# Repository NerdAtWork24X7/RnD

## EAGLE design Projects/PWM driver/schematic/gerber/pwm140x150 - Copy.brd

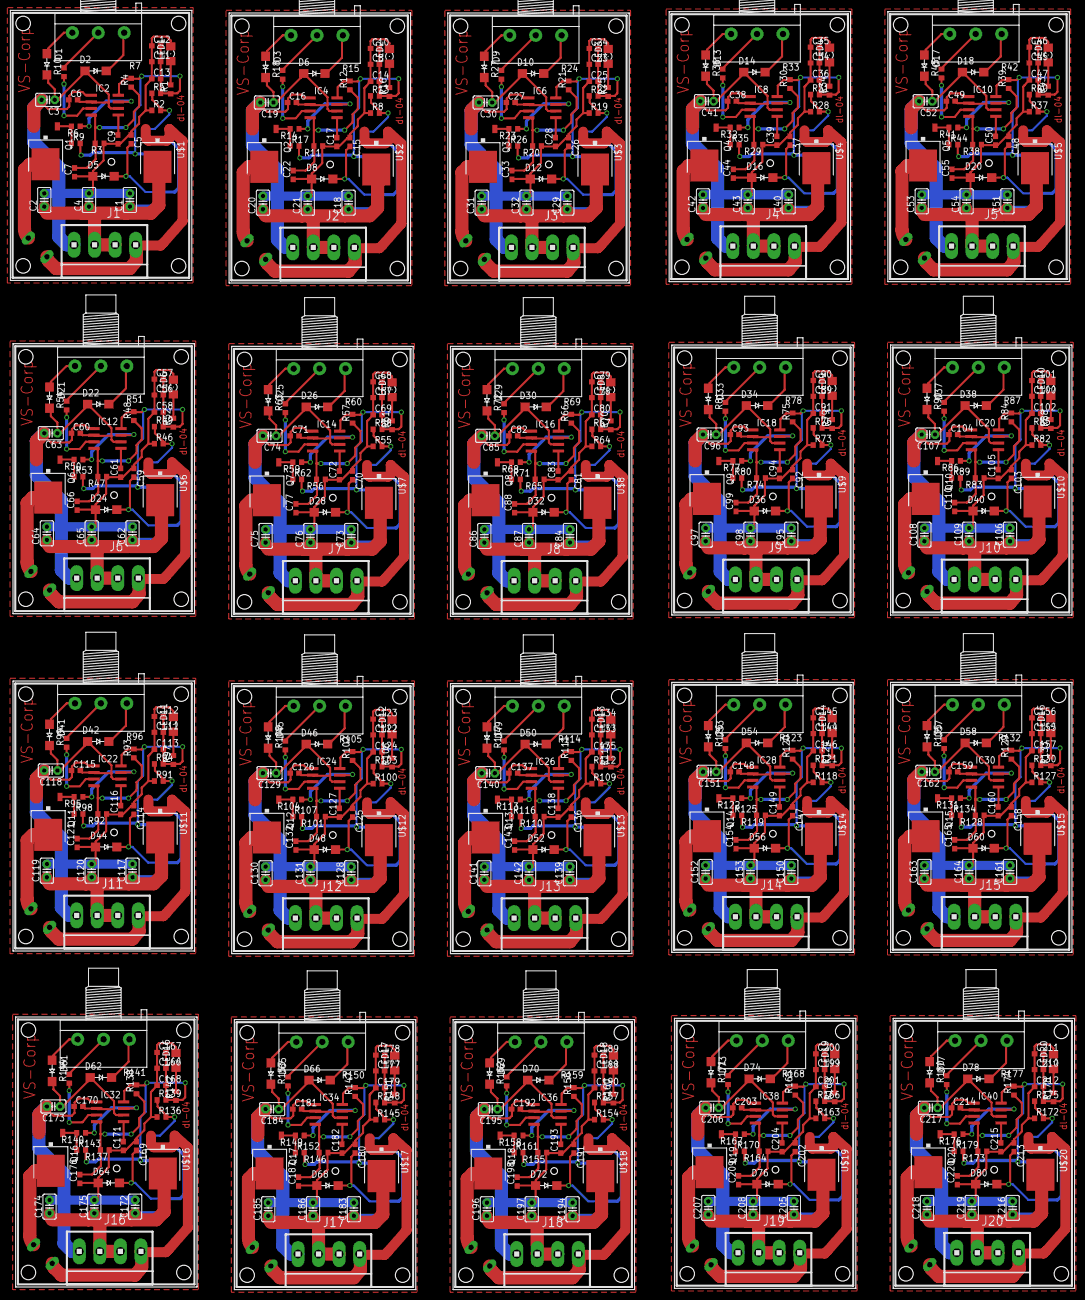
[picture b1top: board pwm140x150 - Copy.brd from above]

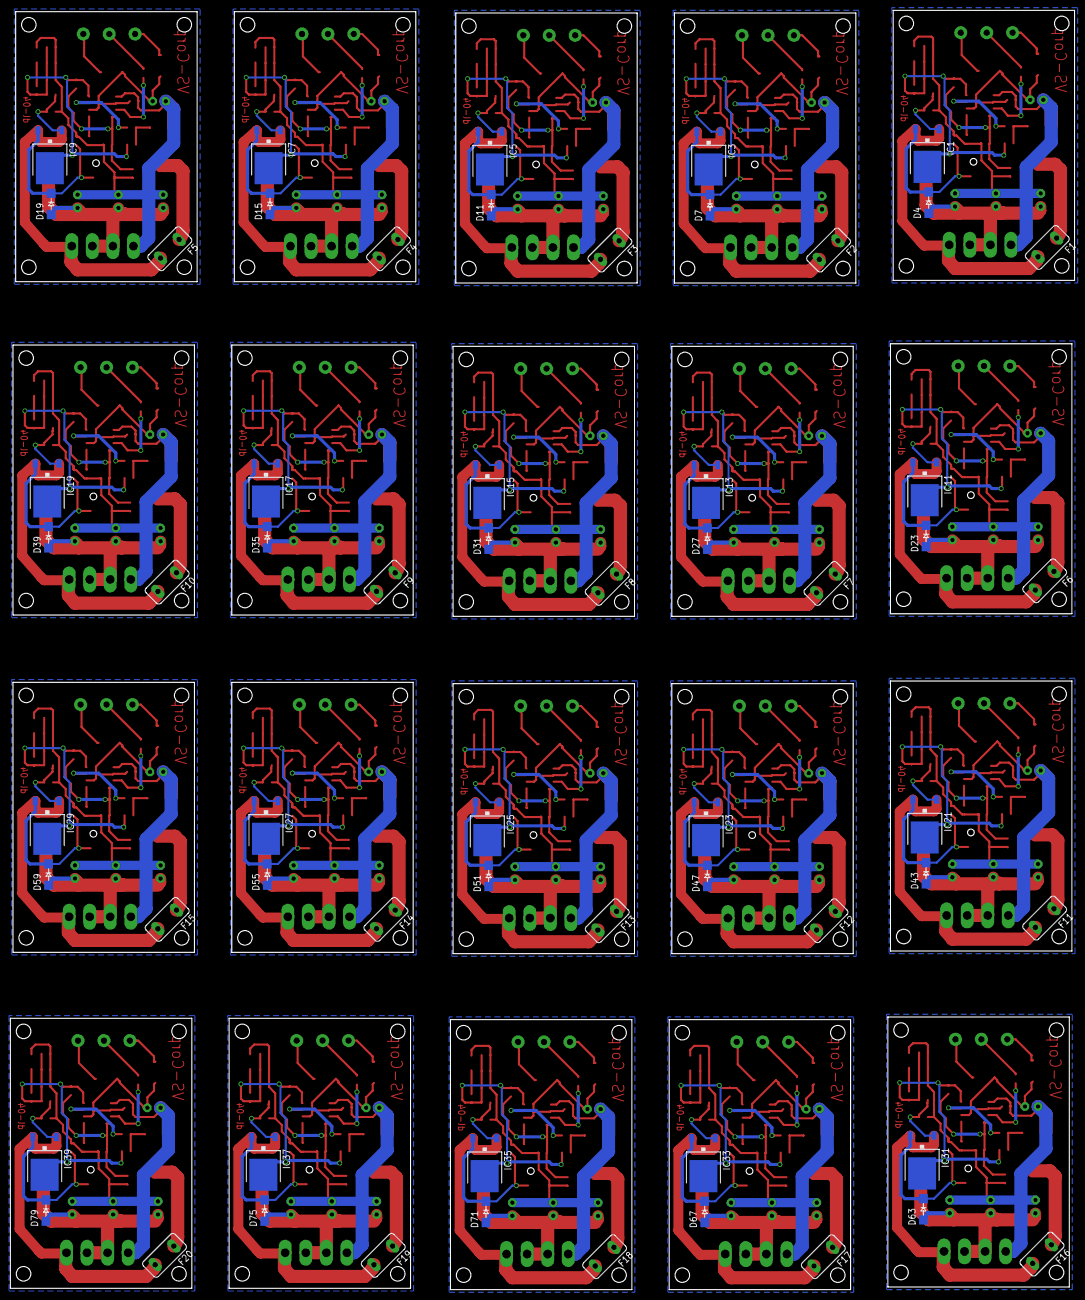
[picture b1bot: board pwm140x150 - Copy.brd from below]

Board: 2 copper layers, 205.2 x 246.6 mm, 620 parts (60 on the bottom side), 340 nets.

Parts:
C1, C18, C29, C40, C51, C62, C73, C84, C95, C106, C117, C128, C139, C150, C161, C172, C183, C194, C205, C216: C025-025X050
C2, C4, C20, C21, C31, C32, C42, C43, C53, C54, C64, C65, C75, C76, C86, C87, C97, C98, C108, C109, C119, C120, C130, C131, C141, C142, C152, C153, C163, C164, C174, C175, C185, C186, C196, C197, C207, C208, C218, C219: 220uf; C025-025X050
C3, C19, C30, C41, C52, C63, C74, C85, C96, C107, C118, C129, C140, C151, C162, C173, C184, C195, C206, C217: 0.1uf; C025-025X050
C5, C15, C26, C37, C48, C59, C70, C81, C92, C103, C114, C125, C136, C147, C158, C169, C180, C191, C202, C213: 100nf; C0603
C6, C16, C27, C38, C49, C60, C71, C82, C93, C104, C115, C126, C137, C148, C159, C170, C181, C192, C203, C214: 0.1uF; C0603
C7, C22, C33, C44, C55, C66, C77, C88, C99, C110, C121, C132, C143, C154, C165, C176, C187, C198, C209, C220: 220uf; C0603
C8, C11, C23, C34, C45, C56, C67, C78, C89, C100, C111, C122, C133, C144, C155, C166, C177, C188, C199, C210: 100nF; C0603
C9, C10, C12, C17, C24, C28, C35, C39, C46, C50, C57, C61, C68, C72, C79, C83, C90, C94, C101, C105, C112, C116, C123, C127, C134, C138, C145, C149, C156, C160, C167, C171, C178, C182, C189, C193, C200, C204, C211, C215: 10nF; C0603
C13, C14, C25, C36, C47, C58, C69, C80, C91, C102, C113, C124, C135, C146, C157, C168, C179, C190, C201, C212: 1uF; C0603
D1, D2, D3, D6, D9, D10, D13, D14, D17, D18, D21, D22, D25, D26, D29, D30, D33, D34, D37, D38, D41, D42, D45, D46, D49, D50, D53, D54, D57, D58, D61, D62, D65, D66, D69, D70, D73, D74, D77, D78: FM4007; SMA-DO214AC
D4, D7, D11, D15, D19, D23, D27, D31, D35, D39, D43, D47, D51, D55, D59, D63, D67, D71, D75, D79: Fm4007; SMA-DO214AC
D5, D8, D12, D16, D20, D24, D28, D32, D36, D40, D44, D48, D52, D56, D60, D64, D68, D72, D76, D80: 1N34; SMA-DO214AC
F1, F2, F3, F4, F5, F6, F7, F8, F9, F10, F11, F12, F13, F14, F15, F16, F17, F18, F19, F20: FUSETE5; TE5
IC1, IC3, IC5, IC7, IC9, IC11, IC13, IC15, IC17, IC19, IC21, IC23, IC25, IC27, IC29, IC31, IC33, IC35, IC37, IC39: 317; DPACK
IC2, IC4, IC6, IC8, IC10, IC12, IC14, IC16, IC18, IC20, IC22, IC24, IC26, IC28, IC30, IC32, IC34, IC36, IC38, IC40: LM555D; SO08
J1, J2, J3, J4, J5, J6, J7, J8, J9, J10, J11, J12, J13, J14, J15, J16, J17, J18, J19, J20: 1X4MTA
LED1, LED2, LED3, LED4, LED5, LED6, LED7, LED8, LED9, LED10, LED11, LED12, LED13, LED14, LED15, LED16, LED17, LED18, LED19, LED20: LED_1206
Q1, Q2, Q3, Q4, Q5, Q6, Q7, Q8, Q9, Q10, Q11, Q12, Q13, Q14, Q15, Q16, Q17, Q18, Q19, Q20: FDD4141TO252; TO252
R1, R5, R13, R16, R22, R25, R31, R34, R40, R43, R49, R52, R58, R61, R67, R70, R76, R79, R85, R88, R94, R97, R103, R106, R112, R115, R121, R124, R130, R133, R139, R142, R148, R151, R157, R160, R166, R169, R175, R178: 470; R0603
R2, R8, R19, R28, R37, R46, R55, R64, R73, R82, R91, R100, R109, R118, R127, R136, R145, R154, R163, R172: 1.5k; R0603
R3, R11, R20, R29, R38, R47, R56, R65, R74, R83, R92, R101, R110, R119, R128, R137, R146, R155, R164, R173: 330k; R0603
R4, R12, R21, R30, R39, R48, R57, R66, R75, R84, R93, R102, R111, R120, R129, R138, R147, R156, R165, R174: 150k; R0603
R6, R14, R23, R32, R41, R50, R59, R68, R77, R86, R95, R104, R113, R122, R131, R140, R149, R158, R167, R176: 1k; R0603
R7, R15, R24, R33, R42, R51, R60, R69, R78, R87, R96, R105, R114, R123, R132, R141, R150, R159, R168, R177: 3RP/1610N
R9, R17, R26, R35, R44, R53, R62, R71, R80, R89, R98, R107, R116, R125, R134, R143, R152, R161, R170, R179: 47k; R0603
R10, R18, R27, R36, R45, R54, R63, R72, R81, R90, R99, R108, R117, R126, R135, R144, R153, R162, R171, R180: 0r0; R0603
U$1, U$2, U$3, U$4, U$5, U$6, U$7, U$8, U$9, U$10, U$11, U$12, U$13, U$14, U$15, U$16, U$17, U$18, U$19, U$20: DIODE; DPACK

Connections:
GND: C1.2, C2.2, C3.2, C4.2, C5.1, C6.1, C7.1, C9.1, C11.1, C12.1, C13.1, D5.A, IC2.1, J1.1, LED1.C, Q1.2, R2.1, R3.1
GND1: C8.1, C10.1, C14.1, C15.1, C16.1, C17.1, C18.2, C19.2, C20.2, C21.2, C22.1, D8.A, IC4.1, J2.1, LED2.C, Q2.2, R8.1, R11.1
GND2: C23.1, C24.1, C25.1, C26.1, C27.1, C28.1, C29.2, C30.2, C31.2, C32.2, C33.1, D12.A, IC6.1, J3.1, LED3.C, Q3.2, R19.1, R20.1
GND3: C34.1, C35.1, C36.1, C37.1, C38.1, C39.1, C40.2, C41.2, C42.2, C43.2, C44.1, D16.A, IC8.1, J4.1, LED4.C, Q4.2, R28.1, R29.1
GND4: C45.1, C46.1, C47.1, C48.1, C49.1, C50.1, C51.2, C52.2, C53.2, C54.2, C55.1, D20.A, IC10.1, J5.1, LED5.C, Q5.2, R37.1, R38.1
GND5: C56.1, C57.1, C58.1, C59.1, C60.1, C61.1, C62.2, C63.2, C64.2, C65.2, C66.1, D24.A, IC12.1, J6.1, LED6.C, Q6.2, R46.1, R47.1
GND6: C67.1, C68.1, C69.1, C70.1, C71.1, C72.1, C73.2, C74.2, C75.2, C76.2, C77.1, D28.A, IC14.1, J7.1, LED7.C, Q7.2, R55.1, R56.1
GND7: C78.1, C79.1, C80.1, C81.1, C82.1, C83.1, C84.2, C85.2, C86.2, C87.2, C88.1, D32.A, IC16.1, J8.1, LED8.C, Q8.2, R64.1, R65.1
GND8: C89.1, C90.1, C91.1, C92.1, C93.1, C94.1, C95.2, C96.2, C97.2, C98.2, C99.1, D36.A, IC18.1, J9.1, LED9.C, Q9.2, R73.1, R74.1
GND9: C100.1, C101.1, C102.1, C103.1, C104.1, C105.1, C106.2, C107.2, C108.2, C109.2, C110.1, D40.A, IC20.1, J10.1, LED10.C, Q10.2, R82.1, R83.1
GND10: C111.1, C112.1, C113.1, C114.1, C115.1, C116.1, C117.2, C118.2, C119.2, C120.2, C121.1, D44.A, IC22.1, J11.1, LED11.C, Q11.2, R91.1, R92.1
GND11: C122.1, C123.1, C124.1, C125.1, C126.1, C127.1, C128.2, C129.2, C130.2, C131.2, C132.1, D48.A, IC24.1, J12.1, LED12.C, Q12.2, R100.1, R101.1
GND12: C133.1, C134.1, C135.1, C136.1, C137.1, C138.1, C139.2, C140.2, C141.2, C142.2, C143.1, D52.A, IC26.1, J13.1, LED13.C, Q13.2, R109.1, R110.1
GND13: C144.1, C145.1, C146.1, C147.1, C148.1, C149.1, C150.2, C151.2, C152.2, C153.2, C154.1, D56.A, IC28.1, J14.1, LED14.C, Q14.2, R118.1, R119.1
GND14: C155.1, C156.1, C157.1, C158.1, C159.1, C160.1, C161.2, C162.2, C163.2, C164.2, C165.1, D60.A, IC30.1, J15.1, LED15.C, Q15.2, R127.1, R128.1
GND15: C166.1, C167.1, C168.1, C169.1, C170.1, C171.1, C172.2, C173.2, C174.2, C175.2, C176.1, D64.A, IC32.1, J16.1, LED16.C, Q16.2, R136.1, R137.1
GND16: C177.1, C178.1, C179.1, C180.1, C181.1, C182.1, C183.2, C184.2, C185.2, C186.2, C187.1, D68.A, IC34.1, J17.1, LED17.C, Q17.2, R145.1, R146.1
GND17: C188.1, C189.1, C190.1, C191.1, C192.1, C193.1, C194.2, C195.2, C196.2, C197.2, C198.1, D72.A, IC36.1, J18.1, LED18.C, Q18.2, R154.1, R155.1
GND18: C199.1, C200.1, C201.1, C202.1, C203.1, C204.1, C205.2, C206.2, C207.2, C208.2, C209.1, D76.A, IC38.1, J19.1, LED19.C, Q19.2, R163.1, R164.1
GND19: C210.1, C211.1, C212.1, C213.1, C214.1, C215.1, C216.2, C217.2, C218.2, C219.2, C220.1, D80.A, IC40.1, J20.1, LED20.C, Q20.2, R172.1, R173.1
unnamed: C7.2, IC2.4, R3.2, R4.1
unnamed: C3.1, C6.2, D1.K, D2.A, IC2.2, IC2.6
unnamed: D1.A, R7.3
unnamed: D2.K, R7.1
unnamed: R7.2, R10.2
unnamed: IC2.3, R10.1
unnamed: C9.2, IC2.5
unnamed: C5.2, D4.K, D5.K, IC1.VIN
unnamed: Q1.1, R6.2, R9.1
unnamed: IC2.7, R6.1
unnamed: LED1.A, R1.2
unnamed: D3.A, R15.3
unnamed: IC1.ADJ, R2.2, R5.1
unnamed: F1.1, Q1.3
unnamed: F1.2, J1.4, U$1.ADJ, U$1.VIN
unnamed: D6.K, R15.1
unnamed: C17.2, IC4.5
unnamed: C16.2, C19.1, D3.K, D6.A, IC4.2, IC4.6
unnamed: Q2.1, R14.2, R17.1
unnamed: C22.2, IC4.4, R11.2, R12.1
unnamed: IC4.3, R18.1
unnamed: IC4.7, R14.1
unnamed: C15.2, D7.K, D8.K, IC3.VIN
unnamed: LED2.A, R16.2
unnamed: IC3.ADJ, R8.2, R13.1
unnamed: F2.1, Q2.3
unnamed: F2.2, J2.4, U$2.ADJ, U$2.VIN
unnamed: R15.2, R18.2
unnamed: D9.A, R24.3
unnamed: D10.K, R24.1
unnamed: C28.2, IC6.5
unnamed: C27.2, C30.1, D9.K, D10.A, IC6.2, IC6.6
unnamed: Q3.1, R23.2, R26.1
unnamed: C33.2, IC6.4, R20.2, R21.1
unnamed: IC6.3, R27.1
unnamed: IC6.7, R23.1
unnamed: C26.2, D11.K, D12.K, IC5.VIN
unnamed: LED3.A, R25.2
unnamed: IC5.ADJ, R19.2, R22.1
unnamed: F3.1, Q3.3
unnamed: F3.2, J3.4, U$3.ADJ, U$3.VIN
unnamed: R24.2, R27.2
unnamed: D13.A, R33.3
unnamed: D14.K, R33.1
unnamed: C39.2, IC8.5
unnamed: C38.2, C41.1, D13.K, D14.A, IC8.2, IC8.6
unnamed: Q4.1, R32.2, R35.1
unnamed: C44.2, IC8.4, R29.2, R30.1
unnamed: IC8.3, R36.1
unnamed: IC8.7, R32.1
unnamed: C37.2, D15.K, D16.K, IC7.VIN
unnamed: LED4.A, R34.2
unnamed: IC7.ADJ, R28.2, R31.1
unnamed: F4.1, Q4.3
unnamed: F4.2, J4.4, U$4.ADJ, U$4.VIN
unnamed: R33.2, R36.2
unnamed: D17.A, R42.3
unnamed: D18.K, R42.1
unnamed: C50.2, IC10.5
unnamed: C49.2, C52.1, D17.K, D18.A, IC10.2, IC10.6
unnamed: Q5.1, R41.2, R44.1
unnamed: C55.2, IC10.4, R38.2, R39.1
unnamed: IC10.3, R45.1
unnamed: IC10.7, R41.1
unnamed: C48.2, D19.K, D20.K, IC9.VIN
unnamed: LED5.A, R43.2
unnamed: IC9.ADJ, R37.2, R40.1
unnamed: F5.1, Q5.3
unnamed: F5.2, J5.4, U$5.ADJ, U$5.VIN
unnamed: R42.2, R45.2
unnamed: D21.A, R51.3
unnamed: D22.K, R51.1
unnamed: C61.2, IC12.5
unnamed: C60.2, C63.1, D21.K, D22.A, IC12.2, IC12.6
unnamed: Q6.1, R50.2, R53.1
unnamed: C66.2, IC12.4, R47.2, R48.1
unnamed: IC12.3, R54.1
unnamed: IC12.7, R50.1
unnamed: C59.2, D23.K, D24.K, IC11.VIN
unnamed: LED6.A, R52.2
unnamed: IC11.ADJ, R46.2, R49.1
unnamed: F6.1, Q6.3
unnamed: F6.2, J6.4, U$6.ADJ, U$6.VIN
unnamed: R51.2, R54.2
unnamed: D25.A, R60.3
unnamed: D26.K, R60.1
unnamed: C72.2, IC14.5
unnamed: C71.2, C74.1, D25.K, D26.A, IC14.2, IC14.6
unnamed: Q7.1, R59.2, R62.1
unnamed: C77.2, IC14.4, R56.2, R57.1
unnamed: IC14.3, R63.1
unnamed: IC14.7, R59.1
unnamed: C70.2, D27.K, D28.K, IC13.VIN
unnamed: LED7.A, R61.2
unnamed: IC13.ADJ, R55.2, R58.1
unnamed: F7.1, Q7.3
unnamed: F7.2, J7.4, U$7.ADJ, U$7.VIN
unnamed: R60.2, R63.2
unnamed: D29.A, R69.3
unnamed: D30.K, R69.1
unnamed: C83.2, IC16.5
unnamed: C82.2, C85.1, D29.K, D30.A, IC16.2, IC16.6
unnamed: Q8.1, R68.2, R71.1
unnamed: C88.2, IC16.4, R65.2, R66.1
unnamed: IC16.3, R72.1
unnamed: IC16.7, R68.1
unnamed: C81.2, D31.K, D32.K, IC15.VIN
unnamed: LED8.A, R70.2
unnamed: IC15.ADJ, R64.2, R67.1
unnamed: F8.1, Q8.3
unnamed: F8.2, J8.4, U$8.ADJ, U$8.VIN
unnamed: R69.2, R72.2
unnamed: D33.A, R78.3
unnamed: D34.K, R78.1
unnamed: C94.2, IC18.5
unnamed: C93.2, C96.1, D33.K, D34.A, IC18.2, IC18.6
unnamed: Q9.1, R77.2, R80.1
unnamed: C99.2, IC18.4, R74.2, R75.1
unnamed: IC18.3, R81.1
unnamed: IC18.7, R77.1
unnamed: C92.2, D35.K, D36.K, IC17.VIN
unnamed: LED9.A, R79.2
unnamed: IC17.ADJ, R73.2, R76.1
unnamed: F9.1, Q9.3
unnamed: F9.2, J9.4, U$9.ADJ, U$9.VIN
unnamed: R78.2, R81.2
unnamed: D37.A, R87.3
unnamed: D38.K, R87.1
unnamed: C105.2, IC20.5
unnamed: C104.2, C107.1, D37.K, D38.A, IC20.2, IC20.6
unnamed: Q10.1, R86.2, R89.1
unnamed: C110.2, IC20.4, R83.2, R84.1
unnamed: IC20.3, R90.1
unnamed: IC20.7, R86.1
unnamed: C103.2, D39.K, D40.K, IC19.VIN
unnamed: LED10.A, R88.2
unnamed: IC19.ADJ, R82.2, R85.1
unnamed: F10.1, Q10.3
unnamed: F10.2, J10.4, U$10.ADJ, U$10.VIN
unnamed: R87.2, R90.2
unnamed: D41.A, R96.3
unnamed: D42.K, R96.1
unnamed: C116.2, IC22.5
unnamed: C115.2, C118.1, D41.K, D42.A, IC22.2, IC22.6
unnamed: Q11.1, R95.2, R98.1
unnamed: C121.2, IC22.4, R92.2, R93.1
unnamed: IC22.3, R99.1
unnamed: IC22.7, R95.1
unnamed: C114.2, D43.K, D44.K, IC21.VIN
unnamed: LED11.A, R97.2
unnamed: IC21.ADJ, R91.2, R94.1
unnamed: F11.1, Q11.3
unnamed: F11.2, J11.4, U$11.ADJ, U$11.VIN
unnamed: R96.2, R99.2
unnamed: D45.A, R105.3
unnamed: D46.K, R105.1
unnamed: C127.2, IC24.5
unnamed: C126.2, C129.1, D45.K, D46.A, IC24.2, IC24.6
unnamed: Q12.1, R104.2, R107.1
unnamed: C132.2, IC24.4, R101.2, R102.1
unnamed: IC24.3, R108.1
unnamed: IC24.7, R104.1
unnamed: C125.2, D47.K, D48.K, IC23.VIN
unnamed: LED12.A, R106.2
unnamed: IC23.ADJ, R100.2, R103.1
unnamed: F12.1, Q12.3
unnamed: F12.2, J12.4, U$12.ADJ, U$12.VIN
unnamed: R105.2, R108.2
unnamed: D49.A, R114.3
unnamed: D50.K, R114.1
unnamed: C138.2, IC26.5
unnamed: C137.2, C140.1, D49.K, D50.A, IC26.2, IC26.6
unnamed: Q13.1, R113.2, R116.1
unnamed: C143.2, IC26.4, R110.2, R111.1
unnamed: IC26.3, R117.1
unnamed: IC26.7, R113.1
unnamed: C136.2, D51.K, D52.K, IC25.VIN
unnamed: LED13.A, R115.2
unnamed: IC25.ADJ, R109.2, R112.1
unnamed: F13.1, Q13.3
unnamed: F13.2, J13.4, U$13.ADJ, U$13.VIN
unnamed: R114.2, R117.2
unnamed: D53.A, R123.3
unnamed: D54.K, R123.1
unnamed: C149.2, IC28.5
unnamed: C148.2, C151.1, D53.K, D54.A, IC28.2, IC28.6
unnamed: Q14.1, R122.2, R125.1
unnamed: C154.2, IC28.4, R119.2, R120.1
unnamed: IC28.3, R126.1
unnamed: IC28.7, R122.1
unnamed: C147.2, D55.K, D56.K, IC27.VIN
unnamed: LED14.A, R124.2
unnamed: IC27.ADJ, R118.2, R121.1
unnamed: F14.1, Q14.3
unnamed: F14.2, J14.4, U$14.ADJ, U$14.VIN
unnamed: R123.2, R126.2
unnamed: D57.A, R132.3
unnamed: D58.K, R132.1
unnamed: C160.2, IC30.5
unnamed: C159.2, C162.1, D57.K, D58.A, IC30.2, IC30.6
unnamed: Q15.1, R131.2, R134.1
unnamed: C165.2, IC30.4, R128.2, R129.1
unnamed: IC30.3, R135.1
unnamed: IC30.7, R131.1
unnamed: C158.2, D59.K, D60.K, IC29.VIN
unnamed: LED15.A, R133.2
unnamed: IC29.ADJ, R127.2, R130.1
unnamed: F15.1, Q15.3
unnamed: F15.2, J15.4, U$15.ADJ, U$15.VIN
unnamed: R132.2, R135.2
unnamed: D61.A, R141.3
unnamed: D62.K, R141.1
unnamed: C171.2, IC32.5
unnamed: C170.2, C173.1, D61.K, D62.A, IC32.2, IC32.6
unnamed: Q16.1, R140.2, R143.1
unnamed: C176.2, IC32.4, R137.2, R138.1
unnamed: IC32.3, R144.1
unnamed: IC32.7, R140.1
unnamed: C169.2, D63.K, D64.K, IC31.VIN
unnamed: LED16.A, R142.2
unnamed: IC31.ADJ, R136.2, R139.1
unnamed: F16.1, Q16.3
unnamed: F16.2, J16.4, U$16.ADJ, U$16.VIN
unnamed: R141.2, R144.2
unnamed: D65.A, R150.3
unnamed: D66.K, R150.1
unnamed: C182.2, IC34.5
unnamed: C181.2, C184.1, D65.K, D66.A, IC34.2, IC34.6
unnamed: Q17.1, R149.2, R152.1
unnamed: C187.2, IC34.4, R146.2, R147.1
unnamed: IC34.3, R153.1
unnamed: IC34.7, R149.1
unnamed: C180.2, D67.K, D68.K, IC33.VIN
unnamed: LED17.A, R151.2
unnamed: IC33.ADJ, R145.2, R148.1
unnamed: F17.1, Q17.3
unnamed: F17.2, J17.4, U$17.ADJ, U$17.VIN
unnamed: R150.2, R153.2
unnamed: D69.A, R159.3
unnamed: D70.K, R159.1
unnamed: C193.2, IC36.5
unnamed: C192.2, C195.1, D69.K, D70.A, IC36.2, IC36.6
unnamed: Q18.1, R158.2, R161.1
unnamed: C198.2, IC36.4, R155.2, R156.1
unnamed: IC36.3, R162.1
unnamed: IC36.7, R158.1
unnamed: C191.2, D71.K, D72.K, IC35.VIN
unnamed: LED18.A, R160.2
unnamed: IC35.ADJ, R154.2, R157.1
unnamed: F18.1, Q18.3
unnamed: F18.2, J18.4, U$18.ADJ, U$18.VIN
unnamed: R159.2, R162.2
unnamed: D73.A, R168.3
unnamed: D74.K, R168.1
unnamed: C204.2, IC38.5
unnamed: C203.2, C206.1, D73.K, D74.A, IC38.2, IC38.6
unnamed: Q19.1, R167.2, R170.1
unnamed: C209.2, IC38.4, R164.2, R165.1
unnamed: IC38.3, R171.1
unnamed: IC38.7, R167.1
unnamed: C202.2, D75.K, D76.K, IC37.VIN
unnamed: LED19.A, R169.2
unnamed: IC37.ADJ, R163.2, R166.1
unnamed: F19.1, Q19.3
unnamed: F19.2, J19.4, U$19.ADJ, U$19.VIN
unnamed: R168.2, R171.2
unnamed: D77.A, R177.3
unnamed: D78.K, R177.1
unnamed: C215.2, IC40.5
unnamed: C214.2, C217.1, D77.K, D78.A, IC40.2, IC40.6
unnamed: Q20.1, R176.2, R179.1
unnamed: C220.2, IC40.4, R173.2, R174.1
unnamed: IC40.3, R180.1
unnamed: IC40.7, R176.1
unnamed: C213.2, D79.K, D80.K, IC39.VIN
unnamed: LED20.A, R178.2
unnamed: IC39.ADJ, R172.2, R175.1
unnamed: F20.1, Q20.3
unnamed: F20.2, J20.4, U$20.ADJ, U$20.VIN
unnamed: R177.2, R180.2
VCC: C11.2, C12.2, C13.2, IC1.VOUT, IC2.8, R1.1, R4.2, R5.2, R9.2
VCC1: C8.2, C10.2, C14.2, IC3.VOUT, IC4.8, R12.2, R13.2, R16.1, R17.2
VCC2: C23.2, C24.2, C25.2, IC5.VOUT, IC6.8, R21.2, R22.2, R25.1, R26.2
VCC3: C34.2, C35.2, C36.2, IC7.VOUT, IC8.8, R30.2, R31.2, R34.1, R35.2
VCC4: C45.2, C46.2, C47.2, IC9.VOUT, IC10.8, R39.2, R40.2, R43.1, R44.2
VCC5: C56.2, C57.2, C58.2, IC11.VOUT, IC12.8, R48.2, R49.2, R52.1, R53.2
VCC6: C67.2, C68.2, C69.2, IC13.VOUT, IC14.8, R57.2, R58.2, R61.1, R62.2
VCC7: C78.2, C79.2, C80.2, IC15.VOUT, IC16.8, R66.2, R67.2, R70.1, R71.2
VCC8: C89.2, C90.2, C91.2, IC17.VOUT, IC18.8, R75.2, R76.2, R79.1, R80.2
VCC9: C100.2, C101.2, C102.2, IC19.VOUT, IC20.8, R84.2, R85.2, R88.1, R89.2
VCC10: C111.2, C112.2, C113.2, IC21.VOUT, IC22.8, R93.2, R94.2, R97.1, R98.2
VCC11: C122.2, C123.2, C124.2, IC23.VOUT, IC24.8, R102.2, R103.2, R106.1, R107.2
VCC12: C133.2, C134.2, C135.2, IC25.VOUT, IC26.8, R111.2, R112.2, R115.1, R116.2
VCC13: C144.2, C145.2, C146.2, IC27.VOUT, IC28.8, R120.2, R121.2, R124.1, R125.2
VCC14: C155.2, C156.2, C157.2, IC29.VOUT, IC30.8, R129.2, R130.2, R133.1, R134.2
VCC15: C166.2, C167.2, C168.2, IC31.VOUT, IC32.8, R138.2, R139.2, R142.1, R143.2
VCC16: C177.2, C178.2, C179.2, IC33.VOUT, IC34.8, R147.2, R148.2, R151.1, R152.2
VCC17: C188.2, C189.2, C190.2, IC35.VOUT, IC36.8, R156.2, R157.2, R160.1, R161.2
VCC18: C199.2, C200.2, C201.2, IC37.VOUT, IC38.8, R165.2, R166.2, R169.1, R170.2
VCC19: C210.2, C211.2, C212.2, IC39.VOUT, IC40.8, R174.2, R175.2, R178.1, R179.2
VDD: C1.1, C2.1, C4.1, D4.A, J1.2, J1.3, U$1.VOUT
VDD1: C18.1, C20.1, C21.1, D7.A, J2.2, J2.3, U$2.VOUT
VDD2: C29.1, C31.1, C32.1, D11.A, J3.2, J3.3, U$3.VOUT
VDD3: C40.1, C42.1, C43.1, D15.A, J4.2, J4.3, U$4.VOUT
VDD4: C51.1, C53.1, C54.1, D19.A, J5.2, J5.3, U$5.VOUT
VDD5: C62.1, C64.1, C65.1, D23.A, J6.2, J6.3, U$6.VOUT
VDD6: C73.1, C75.1, C76.1, D27.A, J7.2, J7.3, U$7.VOUT
VDD7: C84.1, C86.1, C87.1, D31.A, J8.2, J8.3, U$8.VOUT
VDD8: C95.1, C97.1, C98.1, D35.A, J9.2, J9.3, U$9.VOUT
VDD9: C106.1, C108.1, C109.1, D39.A, J10.2, J10.3, U$10.VOUT
VDD10: C117.1, C119.1, C120.1, D43.A, J11.2, J11.3, U$11.VOUT
VDD11: C128.1, C130.1, C131.1, D47.A, J12.2, J12.3, U$12.VOUT
VDD12: C139.1, C141.1, C142.1, D51.A, J13.2, J13.3, U$13.VOUT
VDD13: C150.1, C152.1, C153.1, D55.A, J14.2, J14.3, U$14.VOUT
VDD14: C161.1, C163.1, C164.1, D59.A, J15.2, J15.3, U$15.VOUT
VDD15: C172.1, C174.1, C175.1, D63.A, J16.2, J16.3, U$16.VOUT
VDD16: C183.1, C185.1, C186.1, D67.A, J17.2, J17.3, U$17.VOUT
VDD17: C194.1, C196.1, C197.1, D71.A, J18.2, J18.3, U$18.VOUT
VDD18: C205.1, C207.1, C208.1, D75.A, J19.2, J19.3, U$19.VOUT
VDD19: C216.1, C218.1, C219.1, D79.A, J20.2, J20.3, U$20.VOUT

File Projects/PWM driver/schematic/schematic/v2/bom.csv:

Part,Value,Device,Package,Description,
C1,,C-US025-025X050,C025-025X050,CAPACITOR,
C2,220uf,C-US025-025X050,C025-025X050,CAPACITOR,
C3,0.1uf,C-US025-025X050,C025-025X050,CAPACITOR,
C4,220uf,C-US025-025X050,C025-025X050,CAPACITOR,
C5,100nf,CC0603,C0603,CAPACITOR,
C6,0.1uF,CC0603,C0603,CAPACITOR,
C7,220uf,CC0603,C0603,CAPACITOR,
C9,10nF,CC0603,C0603,CAPACITOR,
C11,100nF,CC0603,C0603,CAPACITOR,
C12,10nF,CC0603,C0603,CAPACITOR,
C13,1uF,CC0603,C0603,CAPACITOR,
D1,FM4007,GF1,SMA-DO214AC,DIODE,
D2,FM4007,GF1,SMA-DO214AC,DIODE,
D4,Fm4007,GF1,SMA-DO214AC,DIODE,
D5,1N34,GF1,SMA-DO214AC,DIODE,
F1,FUSETE5,FUSETE5,TE5,Fuse,
IC1,LM317,317,DPACK,Positive VOLTAGE REGULATOR,
IC2,LM555D,LM555D,SO08,TIMER,
J1,Connector,MTA04-156,1X4MTA,AMP connector,
LED1,,LED_E,LED_1206,LED,
Q1,mosfet,FDD4141TO252,TO252,P-Channel PowerTrench® MOSFET,
R1,1k,RR0603,R0603,RESISTOR,
R2,1.5k,RR0603,R0603,RESISTOR,
R3,330k,RR0603,R0603,RESISTOR,
R4,150k,RR0603,R0603,RESISTOR,
R5,470,RR0603,R0603,RESISTOR,
R6,1k,RR0603,R0603,RESISTOR,
R7,16mm Potentiometer one level,3RP/1610N,3RP/1610N,16mm Potentiometer one level,
R8,0,RR0603,R0603,RESISTOR,donot mount
R9,47k,RR0603,R0603,RESISTOR,
R10,0r0,RR0603,R0603,RESISTOR,
U$1,DIODE D_PAK,DIODE,DPACK,,

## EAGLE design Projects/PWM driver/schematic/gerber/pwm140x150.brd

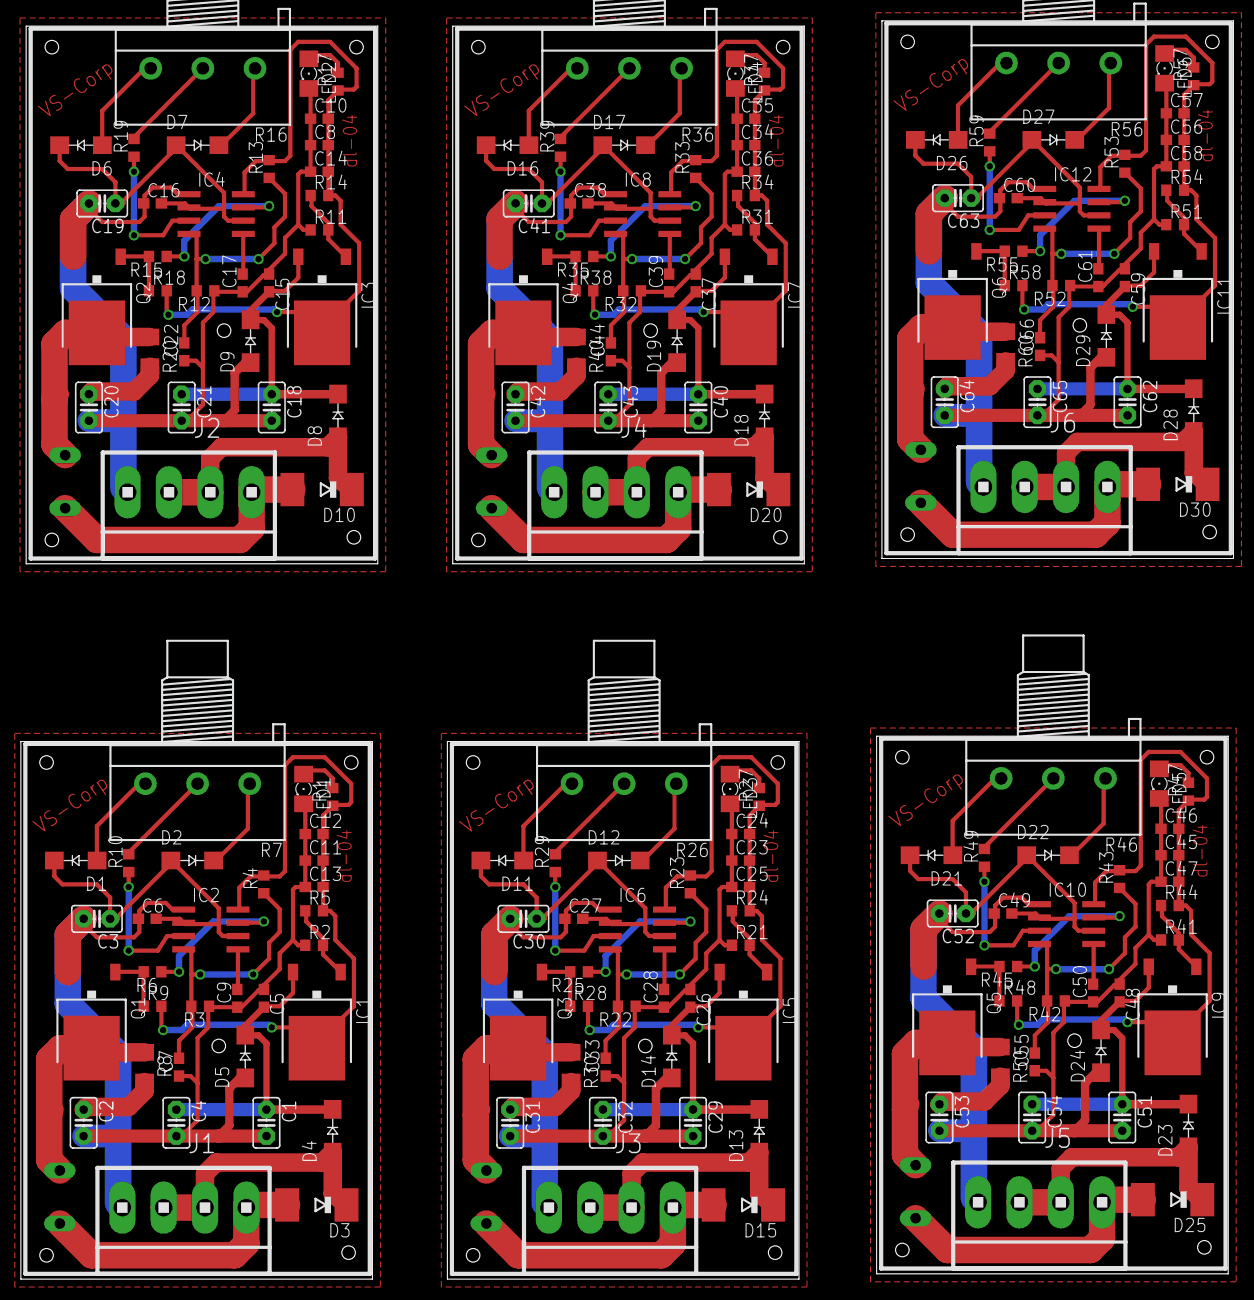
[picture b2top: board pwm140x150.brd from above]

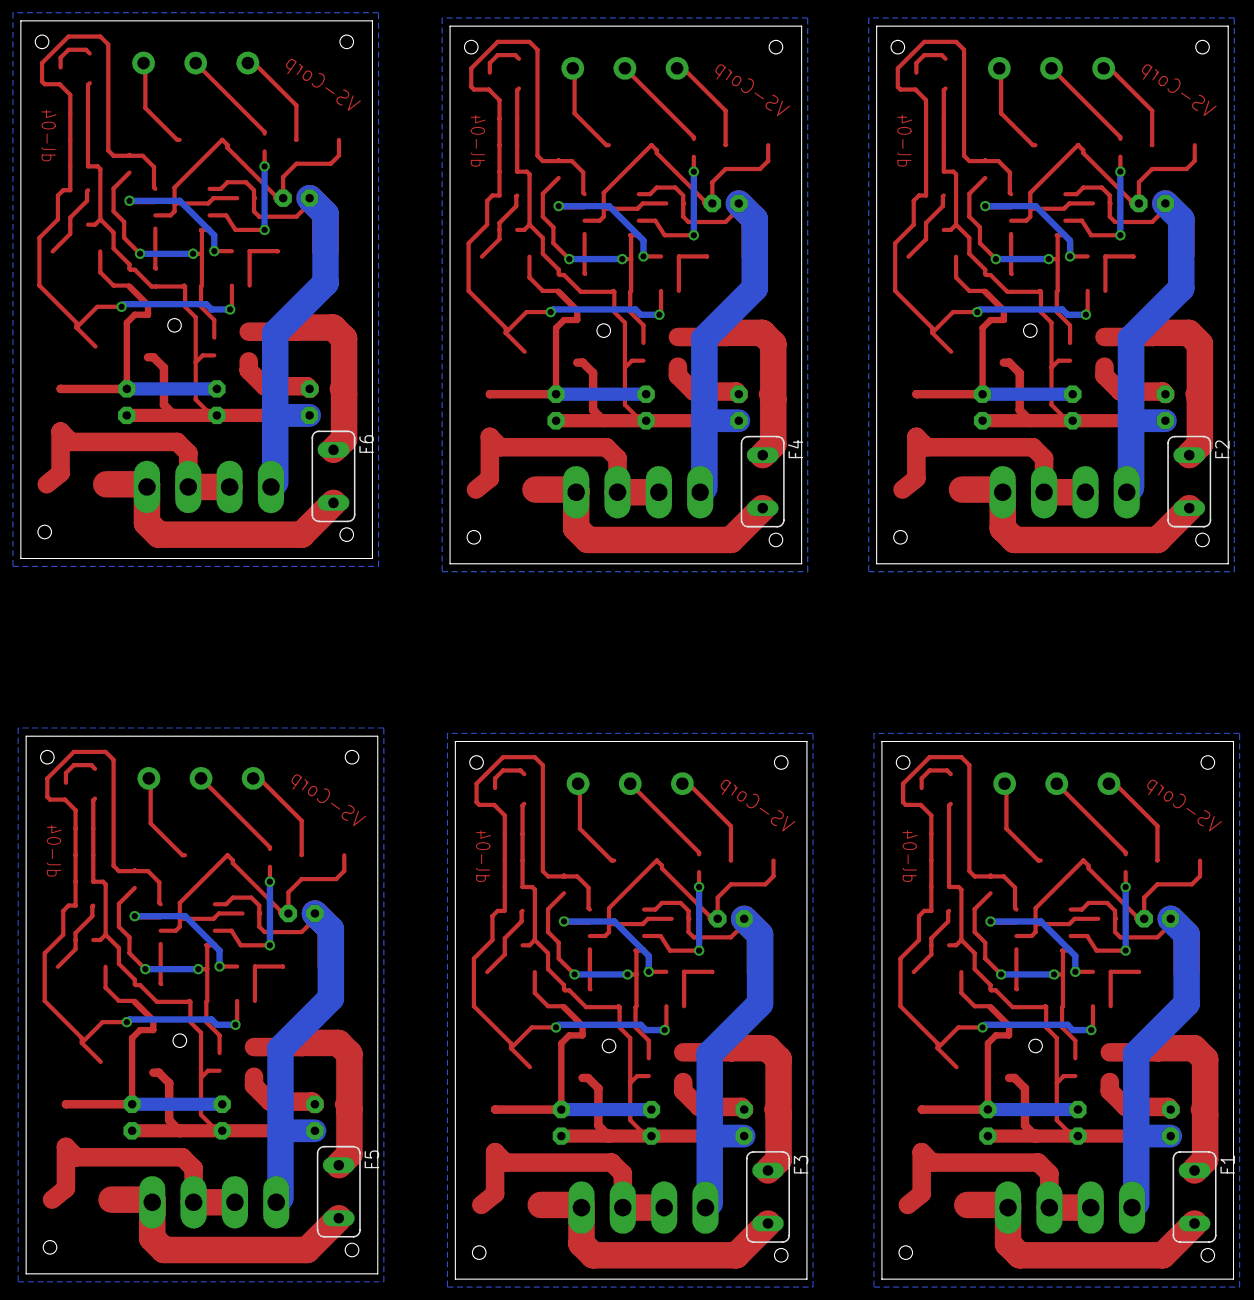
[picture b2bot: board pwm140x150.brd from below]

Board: 2 copper layers, 116.3 x 120.6 mm, 192 parts (6 on the bottom side), 108 nets.

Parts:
C1, C18, C29, C40, C51, C62: C025-025X050
C2, C20, C31, C42, C53, C64: 2.2uf; C025-025X050
C3, C19, C30, C41, C52, C63: 0.1uf; C025-025X050
C4, C21, C32, C43, C54, C65: 220uf; C025-025X050
C5, C15, C26, C37, C48, C59: 100nf; C0603
C6, C16, C27, C38, C49, C60: 0.1uF; C0603
C7, C22, C33, C44, C55, C66: 220uf; C0603
C8, C11, C23, C34, C45, C56: 100nF; C0603
C9, C10, C12, C17, C24, C28, C35, C39, C46, C50, C57, C61: 10nF; C0603
C13, C14, C25, C36, C47, C58: 1uF; C0603
D1, D2, D6, D7, D11, D12, D16, D17, D21, D22, D26, D27: FM4007; SMA-DO214AC
D3, D10, D15, D20, D25, D30: SOD106-W
D4, D8, D13, D18, D23, D28: Fm4007; SMA-DO214AC
D5, D9, D14, D19, D24, D29: 1N34; SMA-DO214AC
F1, F2, F3, F4, F5, F6: FUSETE5; TE5
IC1, IC3, IC5, IC7, IC9, IC11: 317; DPACK
IC2, IC4, IC6, IC8, IC10, IC12: LM555D; SO08
J1, J2, J3, J4, J5, J6: 1X4MTA
LED1, LED2, LED3, LED4, LED5, LED6: LED_1206
Q1, Q2, Q3, Q4, Q5, Q6: FDD4141TO252; TO252
R1, R5, R14, R17, R24, R27, R34, R37, R44, R47, R54, R57: 470; R0603
R2, R11, R21, R31, R41, R51: 1.5k; R0603
R3, R12, R22, R32, R42, R52: 330k; R0603
R4, R13, R23, R33, R43, R53: 150k; R0603
R6, R15, R25, R35, R45, R55: 1k; R0603
R7, R16, R26, R36, R46, R56: 3RP/1610N
R8, R20, R30, R40, R50, R60: 100; R1206
R9, R18, R28, R38, R48, R58: 47k; R0603
R10, R19, R29, R39, R49, R59: 0r0; R0603

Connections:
GND: C1.2, C2.2, C3.2, C4.2, C5.1, C6.1, C7.1, C9.1, C11.1, C12.1, C13.1, D5.A, IC2.1, J1.1, LED1.C, Q1.2, R2.1, R3.1
GND1: C8.1, C10.1, C14.1, C15.1, C16.1, C17.1, C18.2, C19.2, C20.2, C21.2, C22.1, D9.A, IC4.1, J2.1, LED2.C, Q2.2, R11.1, R12.1
GND2: C23.1, C24.1, C25.1, C26.1, C27.1, C28.1, C29.2, C30.2, C31.2, C32.2, C33.1, D14.A, IC6.1, J3.1, LED3.C, Q3.2, R21.1, R22.1
GND3: C34.1, C35.1, C36.1, C37.1, C38.1, C39.1, C40.2, C41.2, C42.2, C43.2, C44.1, D19.A, IC8.1, J4.1, LED4.C, Q4.2, R31.1, R32.1
GND4: C45.1, C46.1, C47.1, C48.1, C49.1, C50.1, C51.2, C52.2, C53.2, C54.2, C55.1, D24.A, IC10.1, J5.1, LED5.C, Q5.2, R41.1, R42.1
GND5: C56.1, C57.1, C58.1, C59.1, C60.1, C61.1, C62.2, C63.2, C64.2, C65.2, C66.1, D29.A, IC12.1, J6.1, LED6.C, Q6.2, R51.1, R52.1
unnamed: C7.2, IC2.4, R3.2, R4.1
unnamed: C3.1, C6.2, D1.K, D2.A, IC2.2, IC2.6
unnamed: D1.A, R7.3
unnamed: D2.K, R7.1
unnamed: R7.2, R10.2
unnamed: IC2.3, R10.1
unnamed: C9.2, IC2.5
unnamed: C1.1, C4.1, C5.2, D4.K, D5.K, IC1.VIN
unnamed: Q1.1, R6.2, R9.1
unnamed: IC2.7, R6.1
unnamed: LED1.A, R1.2
unnamed: C2.1, R8.2
unnamed: IC1.ADJ, R2.2, R5.1
unnamed: F1.1, Q1.3, R8.1
unnamed: D3.A, F1.2, J1.4
unnamed: D6.A, R16.3
unnamed: D7.K, R16.1
unnamed: C17.2, IC4.5
unnamed: C16.2, C19.1, D6.K, D7.A, IC4.2, IC4.6
unnamed: Q2.1, R15.2, R18.1
unnamed: C22.2, IC4.4, R12.2, R13.1
unnamed: IC4.3, R19.1
unnamed: IC4.7, R15.1
unnamed: C15.2, C18.1, C21.1, D8.K, D9.K, IC3.VIN
unnamed: LED2.A, R17.2
unnamed: IC3.ADJ, R11.2, R14.1
unnamed: F2.1, Q2.3, R20.1
unnamed: D10.A, F2.2, J2.4
unnamed: R16.2, R19.2
unnamed: C20.1, R20.2
unnamed: D11.A, R26.3
unnamed: D12.K, R26.1
unnamed: C28.2, IC6.5
unnamed: C27.2, C30.1, D11.K, D12.A, IC6.2, IC6.6
unnamed: Q3.1, R25.2, R28.1
unnamed: C33.2, IC6.4, R22.2, R23.1
unnamed: IC6.3, R29.1
unnamed: IC6.7, R25.1
unnamed: C26.2, C29.1, C32.1, D13.K, D14.K, IC5.VIN
unnamed: LED3.A, R27.2
unnamed: IC5.ADJ, R21.2, R24.1
unnamed: F3.1, Q3.3, R30.1
unnamed: D15.A, F3.2, J3.4
unnamed: R26.2, R29.2
unnamed: C31.1, R30.2
unnamed: D16.A, R36.3
unnamed: D17.K, R36.1
unnamed: C39.2, IC8.5
unnamed: C38.2, C41.1, D16.K, D17.A, IC8.2, IC8.6
unnamed: Q4.1, R35.2, R38.1
unnamed: C44.2, IC8.4, R32.2, R33.1
unnamed: IC8.3, R39.1
unnamed: IC8.7, R35.1
unnamed: C37.2, C40.1, C43.1, D18.K, D19.K, IC7.VIN
unnamed: LED4.A, R37.2
unnamed: IC7.ADJ, R31.2, R34.1
unnamed: F4.1, Q4.3, R40.1
unnamed: D20.A, F4.2, J4.4
unnamed: R36.2, R39.2
unnamed: C42.1, R40.2
unnamed: D21.A, R46.3
unnamed: D22.K, R46.1
unnamed: C50.2, IC10.5
unnamed: C49.2, C52.1, D21.K, D22.A, IC10.2, IC10.6
unnamed: Q5.1, R45.2, R48.1
unnamed: C55.2, IC10.4, R42.2, R43.1
unnamed: IC10.3, R49.1
unnamed: IC10.7, R45.1
unnamed: C48.2, C51.1, C54.1, D23.K, D24.K, IC9.VIN
unnamed: LED5.A, R47.2
unnamed: IC9.ADJ, R41.2, R44.1
unnamed: F5.1, Q5.3, R50.1
unnamed: D25.A, F5.2, J5.4
unnamed: R46.2, R49.2
unnamed: C53.1, R50.2
unnamed: D26.A, R56.3
unnamed: D27.K, R56.1
unnamed: C61.2, IC12.5
unnamed: C60.2, C63.1, D26.K, D27.A, IC12.2, IC12.6
unnamed: Q6.1, R55.2, R58.1
unnamed: C66.2, IC12.4, R52.2, R53.1
unnamed: IC12.3, R59.1
unnamed: IC12.7, R55.1
unnamed: C59.2, C62.1, C65.1, D28.K, D29.K, IC11.VIN
unnamed: LED6.A, R57.2
unnamed: IC11.ADJ, R51.2, R54.1
unnamed: F6.1, Q6.3, R60.1
unnamed: D30.A, F6.2, J6.4
unnamed: R56.2, R59.2
unnamed: C64.1, R60.2
VCC: C11.2, C12.2, C13.2, IC1.VOUT, IC2.8, R1.1, R4.2, R5.2, R9.2
VCC1: C8.2, C10.2, C14.2, IC3.VOUT, IC4.8, R13.2, R14.2, R17.1, R18.2
VCC2: C23.2, C24.2, C25.2, IC5.VOUT, IC6.8, R23.2, R24.2, R27.1, R28.2
VCC3: C34.2, C35.2, C36.2, IC7.VOUT, IC8.8, R33.2, R34.2, R37.1, R38.2
VCC4: C45.2, C46.2, C47.2, IC9.VOUT, IC10.8, R43.2, R44.2, R47.1, R48.2
VCC5: C56.2, C57.2, C58.2, IC11.VOUT, IC12.8, R53.2, R54.2, R57.1, R58.2
VDD: D3.C, D4.A, J1.2, J1.3
VDD1: D8.A, D10.C, J2.2, J2.3
VDD2: D13.A, D15.C, J3.2, J3.3
VDD3: D18.A, D20.C, J4.2, J4.3
VDD4: D23.A, D25.C, J5.2, J5.3
VDD5: D28.A, D30.C, J6.2, J6.3

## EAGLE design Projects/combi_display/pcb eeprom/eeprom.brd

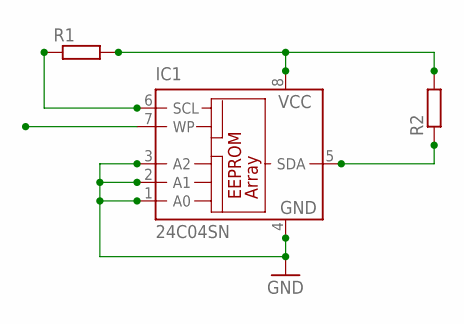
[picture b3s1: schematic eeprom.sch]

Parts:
IC1: 24C04SN; SO-08
R1, R2: R-EU_R2012W; R2012W

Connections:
GND: IC1.1 (A0), IC1.2 (A1), IC1.3 (A2), IC1.4 (GND)
unnamed: IC1.8 (VCC), R1.2, R2.2
unnamed: IC1.6 (SCL), R1.1
unnamed: IC1.5 (SDA), R2.1

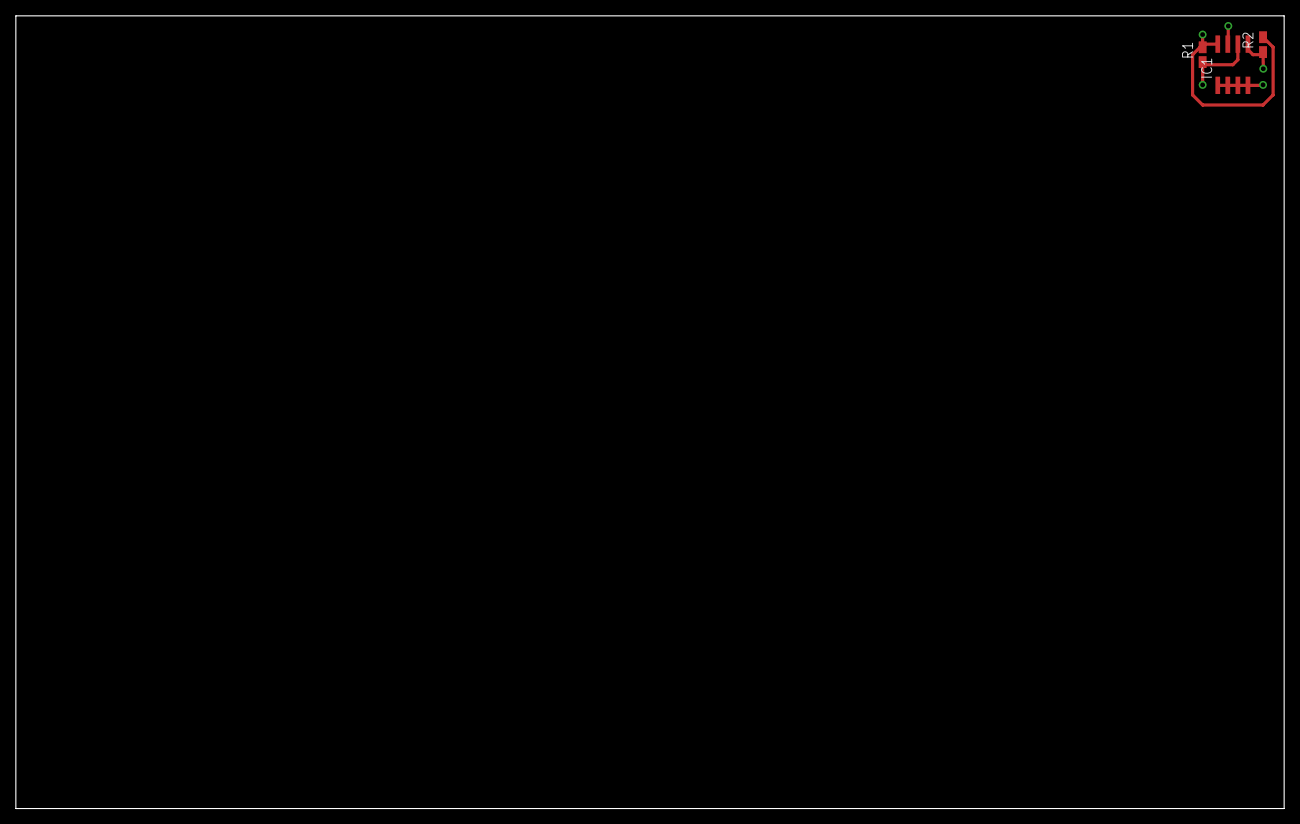
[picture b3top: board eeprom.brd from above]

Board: 2 copper layers, 160.0 x 100.0 mm, 3 parts (0 on the bottom side), 4 nets.
